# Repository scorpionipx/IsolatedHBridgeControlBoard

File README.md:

# IsolatedHBridgeControlBoard
Circuit used to control up to 4 H Bridges using optocouplers

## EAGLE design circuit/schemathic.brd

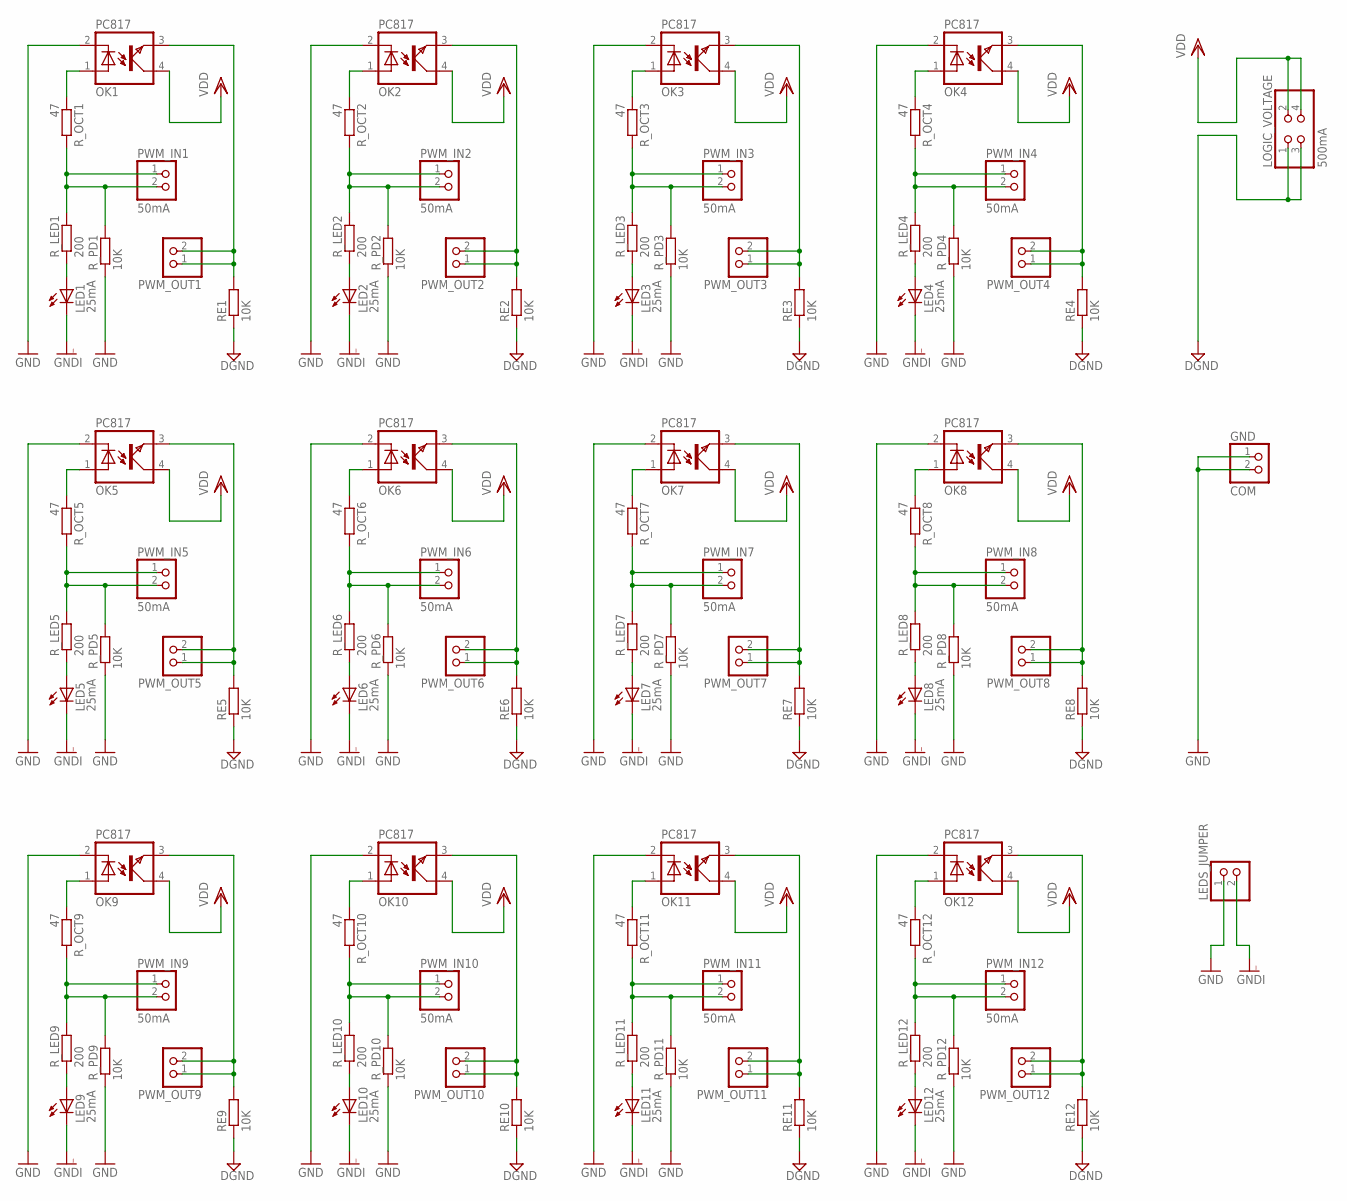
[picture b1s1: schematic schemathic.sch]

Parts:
GND: COM; 1X02
LED1, LED2, LED3, LED4, LED5, LED6, LED7, LED8, LED9, LED10, LED11, LED12: 25mA; LED3MM
LEDS_JUMPER: PINHD-1X2; 1X02
LOGIC_VOLTAGE: 500mA; 2X02
OK1, OK2, OK3, OK4, OK5, OK6, OK7, OK8, OK9, OK10, OK11, OK12: PC817; DIL04
PWM_IN1, PWM_IN2, PWM_IN3, PWM_IN4, PWM_IN5, PWM_IN6, PWM_IN7, PWM_IN8, PWM_IN9, PWM_IN10, PWM_IN11, PWM_IN12: 50mA; 1X02
PWM_OUT1, PWM_OUT2, PWM_OUT3, PWM_OUT4, PWM_OUT5, PWM_OUT6, PWM_OUT7, PWM_OUT8, PWM_OUT9, PWM_OUT10, PWM_OUT11, PWM_OUT12: PINHD-1X2; 1X02
RE1, RE2, RE3, RE4, RE5, RE6, RE7, RE8, RE9, RE10, RE11, RE12: 10K; 0204/7
R_LED1, R_LED2, R_LED3, R_LED4, R_LED5, R_LED6, R_LED7, R_LED8, R_LED9, R_LED10, R_LED11, R_LED12: 200; 0204/7
R_OCT1, R_OCT2, R_OCT3, R_OCT4, R_OCT5, R_OCT6, R_OCT7, R_OCT8, R_OCT9, R_OCT10, R_OCT11, R_OCT12: 47; 0204/7
R_PD1, R_PD2, R_PD3, R_PD4, R_PD5, R_PD6, R_PD7, R_PD8, R_PD9, R_PD10, R_PD11, R_PD12: 10K; 0204/7

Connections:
DGND: LOGIC_VOLTAGE.1, LOGIC_VOLTAGE.3, RE1.1, RE2.1, RE3.1, RE4.1, RE5.1, RE6.1, RE7.1, RE8.1, RE9.1, RE10.1, RE11.1, RE12.1
GND: GND.1, GND.2, LEDS_JUMPER.1, OK1.2 (C), OK2.2 (C), OK3.2 (C), OK4.2 (C), OK5.2 (C), OK6.2 (C), OK7.2 (C), OK8.2 (C), OK9.2 (C), OK10.2 (C), OK11.2 (C), OK12.2 (C), R_PD1.1, R_PD2.1, R_PD3.1, R_PD4.1, R_PD5.1, R_PD6.1, R_PD7.1, R_PD8.1, R_PD9.1, R_PD10.1, R_PD11.1, R_PD12.1
GNDI: LED1.K (C), LED2.K (C), LED3.K (C), LED4.K (C), LED5.K (C), LED6.K (C), LED7.K (C), LED8.K (C), LED9.K (C), LED10.K (C), LED11.K (C), LED12.K (C), LEDS_JUMPER.2
unnamed: LED2.A, R_LED2.1
unnamed: LED1.A, R_LED1.1
unnamed: PWM_IN1.1, PWM_IN1.2, R_LED1.2, R_OCT1.2, R_PD1.2
unnamed: OK1.1 (A), R_OCT1.1
unnamed: OK1.3 (EMIT), PWM_OUT1.1, PWM_OUT1.2, RE1.2
unnamed: PWM_IN2.1, PWM_IN2.2, R_LED2.2, R_OCT2.2, R_PD2.2
unnamed: OK2.1 (A), R_OCT2.1
unnamed: OK2.3 (EMIT), PWM_OUT2.1, PWM_OUT2.2, RE2.2
unnamed: LED3.A, R_LED3.1
unnamed: PWM_IN3.1, PWM_IN3.2, R_LED3.2, R_OCT3.2, R_PD3.2
unnamed: OK3.1 (A), R_OCT3.1
unnamed: OK3.3 (EMIT), PWM_OUT3.1, PWM_OUT3.2, RE3.2
unnamed: LED4.A, R_LED4.1
unnamed: PWM_IN4.1, PWM_IN4.2, R_LED4.2, R_OCT4.2, R_PD4.2
unnamed: OK4.1 (A), R_OCT4.1
unnamed: OK4.3 (EMIT), PWM_OUT4.1, PWM_OUT4.2, RE4.2
unnamed: LED5.A, R_LED5.1
unnamed: PWM_IN5.1, PWM_IN5.2, R_LED5.2, R_OCT5.2, R_PD5.2
unnamed: OK5.1 (A), R_OCT5.1
unnamed: OK5.3 (EMIT), PWM_OUT5.1, PWM_OUT5.2, RE5.2
unnamed: LED6.A, R_LED6.1
unnamed: PWM_IN6.1, PWM_IN6.2, R_LED6.2, R_OCT6.2, R_PD6.2
unnamed: OK6.1 (A), R_OCT6.1
unnamed: OK6.3 (EMIT), PWM_OUT6.1, PWM_OUT6.2, RE6.2
unnamed: LED7.A, R_LED7.1
unnamed: PWM_IN7.1, PWM_IN7.2, R_LED7.2, R_OCT7.2, R_PD7.2
unnamed: OK7.1 (A), R_OCT7.1
unnamed: OK7.3 (EMIT), PWM_OUT7.1, PWM_OUT7.2, RE7.2
unnamed: LED8.A, R_LED8.1
unnamed: PWM_IN8.1, PWM_IN8.2, R_LED8.2, R_OCT8.2, R_PD8.2
unnamed: OK8.1 (A), R_OCT8.1
unnamed: OK8.3 (EMIT), PWM_OUT8.1, PWM_OUT8.2, RE8.2
unnamed: LED9.A, R_LED9.1
unnamed: PWM_IN9.1, PWM_IN9.2, R_LED9.2, R_OCT9.2, R_PD9.2
unnamed: OK9.1 (A), R_OCT9.1
unnamed: OK9.3 (EMIT), PWM_OUT9.1, PWM_OUT9.2, RE9.2
unnamed: LED10.A, R_LED10.1
unnamed: PWM_IN10.1, PWM_IN10.2, R_LED10.2, R_OCT10.2, R_PD10.2
unnamed: OK10.1 (A), R_OCT10.1
unnamed: OK10.3 (EMIT), PWM_OUT10.1, PWM_OUT10.2, RE10.2
unnamed: LED11.A, R_LED11.1
unnamed: PWM_IN11.1, PWM_IN11.2, R_LED11.2, R_OCT11.2, R_PD11.2
unnamed: OK11.1 (A), R_OCT11.1
unnamed: OK11.3 (EMIT), PWM_OUT11.1, PWM_OUT11.2, RE11.2
unnamed: LED12.A, R_LED12.1
unnamed: PWM_IN12.1, PWM_IN12.2, R_LED12.2, R_OCT12.2, R_PD12.2
unnamed: OK12.1 (A), R_OCT12.1
unnamed: OK12.3 (EMIT), PWM_OUT12.1, PWM_OUT12.2, RE12.2
VDD: LOGIC_VOLTAGE.2, LOGIC_VOLTAGE.4, OK1.4 (COL), OK2.4 (COL), OK3.4 (COL), OK4.4 (COL), OK5.4 (COL), OK6.4 (COL), OK7.4 (COL), OK8.4 (COL), OK9.4 (COL), OK10.4 (COL), OK11.4 (COL), OK12.4 (COL)

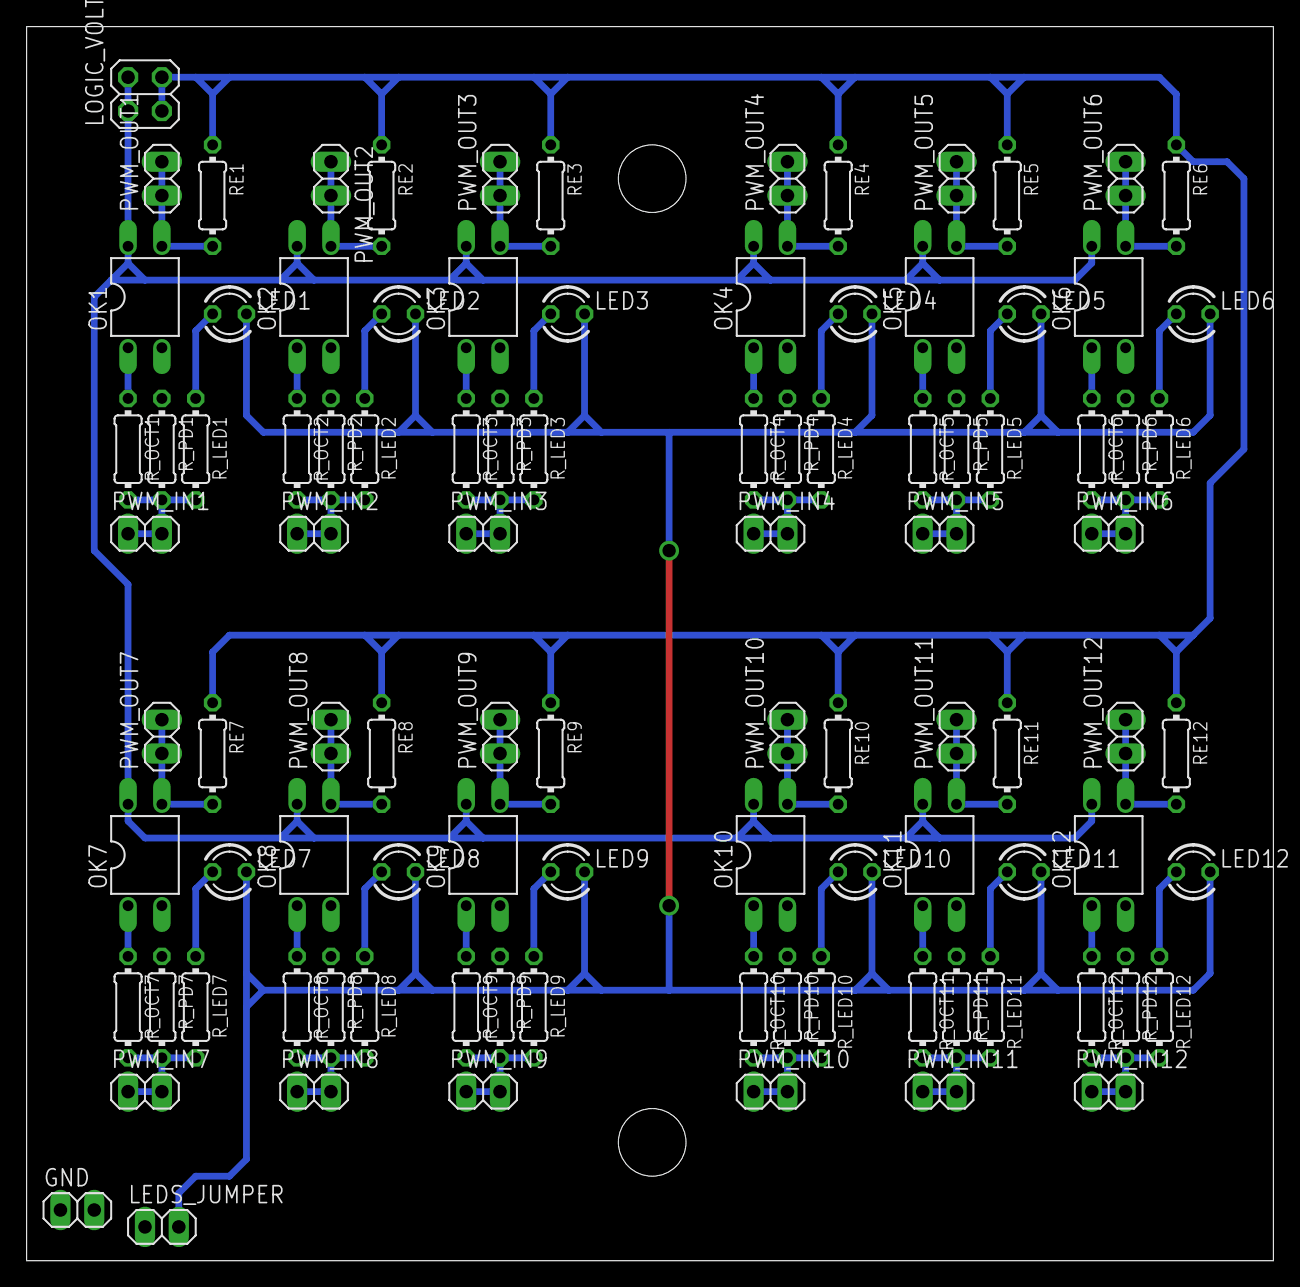
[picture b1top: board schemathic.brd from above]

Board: 2 copper layers, 93.6 x 92.7 mm, 99 parts (0 on the bottom side), 52 nets.

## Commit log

2018-10-01 simulation
2018-10-01 system
2018-10-01 circuit
